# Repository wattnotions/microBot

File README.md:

# microBot
A tiny robot made using micro stepper motors

Here is a video of the v2 test PCB: 
https://www.youtube.com/watch?v=kQc0UNII-Kc

v3 will run on a 800mAh single cell lipo, esp32, lipo charger, tcrt5000 IR sensor, 2 H-bridge driver chips and a mini USB port
for programming and charging the battery.

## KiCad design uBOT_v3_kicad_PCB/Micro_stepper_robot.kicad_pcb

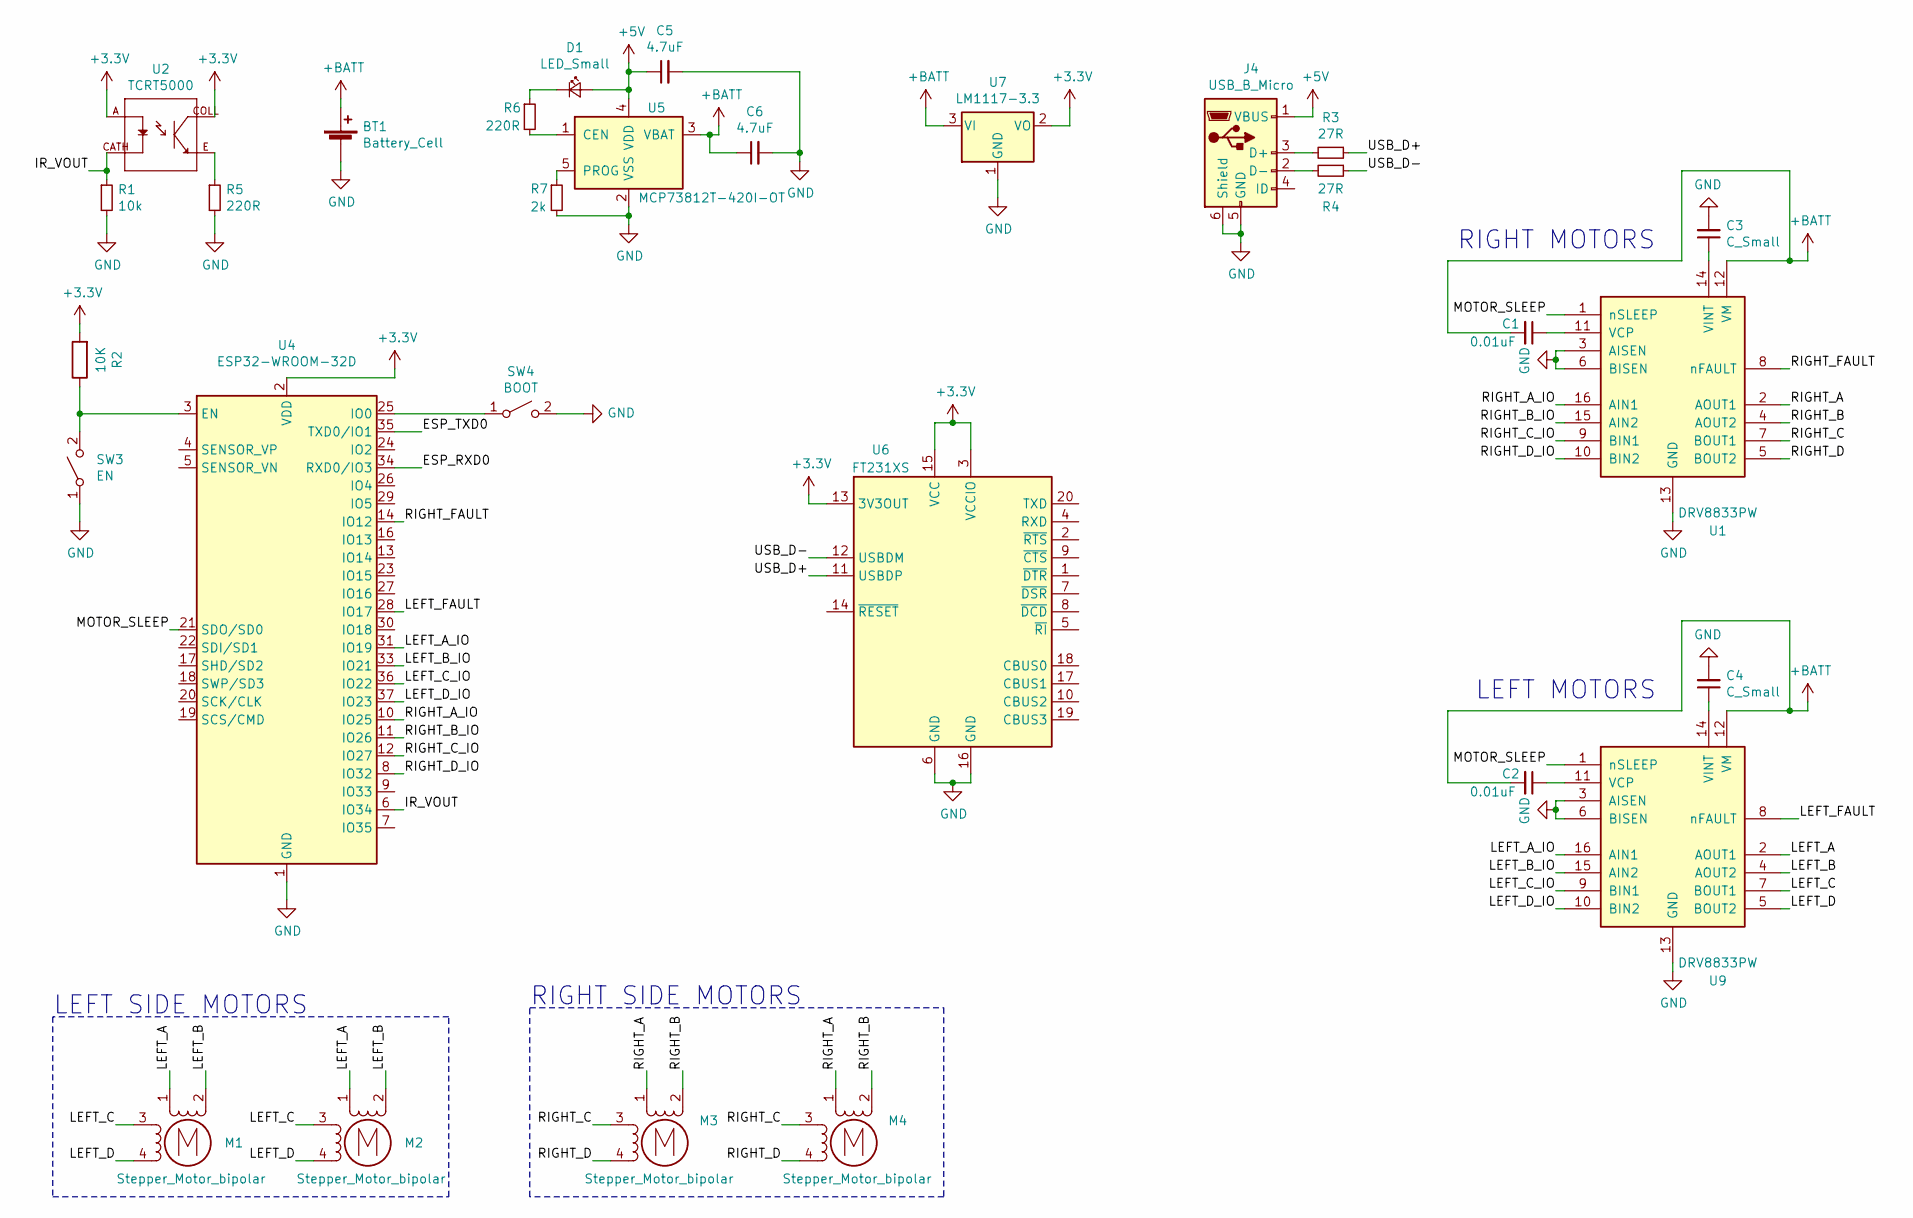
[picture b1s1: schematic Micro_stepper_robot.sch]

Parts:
BT1: Battery_Cell; Molex_PicoBlade_53398-0271_1x02-1MP_P1.25mm_Vertical
C1, C2: 0.01uF; C_0805_2012Metric_Pad1.15x1.40mm_HandSolder
C3, C4: C_Small; C_0805_2012Metric_Pad1.15x1.40mm_HandSolder
C5, C6: 4.7uF; C_0805_2012Metric_Pad1.15x1.40mm_HandSolder
D1: LED_Small; LED_0603_1608Metric
J4: USB_B_Micro; USB_Micro-B_Molex-105133-0001
M1, M2, M3, M4: Stepper_Motor_bipolar; micro_stepper1
R1: 10k; R_0805_2012Metric_Pad1.15x1.40mm_HandSolder
R2: 10K; R_0805_2012Metric_Pad1.15x1.40mm_HandSolder
R3, R4: 27R; R_0805_2012Metric_Pad1.15x1.40mm_HandSolder
R5, R6: 220R; R_0805_2012Metric_Pad1.15x1.40mm_HandSolder
R7: 2k; R_0805_2012Metric_Pad1.15x1.40mm_HandSolder
SW3: EN; SW_SPST_B3U-1000P
SW4: BOOT; SW_SPST_B3U-1000P
U1, U9: DRV8833PW; TSSOP-16_4.4x5mm_P0.65mm
U2: TCRT5000; OPTO_TCRT5000
U4: ESP32-WROOM-32D; ESP32-WROOM-32
U5: MCP73812T-420I-OT; SOT-23-5
U6: FT231XS; SSOP-20_3.9x8.7mm_P0.635mm
U7: LM1117-3.3; SOT-223-3_TabPin2

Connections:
+3V3: R2.2, U2.A, U2.COLL, U4.2 (VDD), U6.3 (VCCIO), U6.13 (3V3OUT), U6.15 (VCC), U7.2 (VO); also elsewhere on the board
+5V: C5.1, D1.2 (A), J4.1 (VBUS), U5.4 (VDD)
+BATT: BT1.1 (+), C1.2, C2.2, C6.1, U1.12 (VM), U5.3 (VBAT), U7.3 (VI), U9.12 (VM); also elsewhere on the board
/ESP_RXD0: U4.34 (RXD0/IO3)
/ESP_TXD0: U4.35 (TXD0/IO1)
/IR_VOUT: R1.1, U2.CATH, U4.6 (IO34)
/LEFT_A: M1.1, M2.1, U9.2 (AOUT1)
/LEFT_A_IO: U4.31 (IO19), U9.16 (AIN1)
/LEFT_B: M1.2 (-), M2.2 (-), U9.4 (AOUT2)
/LEFT_B_IO: U4.33 (IO21), U9.15 (AIN2)
/LEFT_C: M1.3, M2.3, U9.7 (BOUT1)
/LEFT_C_IO: U4.36 (IO22), U9.9 (BIN1)
/LEFT_D: M1.4, M2.4, U9.5 (BOUT2)
/LEFT_D_IO: U4.37 (IO23), U9.10 (BIN2)
/LEFT_FAULT: U4.28 (IO17), U9.8 (nFAULT)
/MOTOR_SLEEP: U1.1 (nSLEEP), U4.21 (SDO/SD0), U9.1 (nSLEEP)
/RIGHT_A: M3.1, M4.1, U1.2 (AOUT1)
/RIGHT_A_IO: U1.16 (AIN1), U4.10 (IO25)
/RIGHT_B: M3.2 (-), M4.2 (-), U1.4 (AOUT2)
/RIGHT_B_IO: U1.15 (AIN2), U4.11 (IO26)
/RIGHT_C: M3.3, M4.3, U1.7 (BOUT1)
/RIGHT_C_IO: U1.9 (BIN1), U4.12 (IO27)
/RIGHT_D: M3.4, M4.4, U1.5 (BOUT2)
/RIGHT_D_IO: U1.10 (BIN2), U4.8 (IO32)
/RIGHT_FAULT: U1.8 (nFAULT), U4.14 (IO12)
/USB_D+: R3.1, U6.11 (USBDP)
/USB_D-: R4.1, U6.12 (USBDM)
GND: BT1.2 (-), C3.2, C4.2, C5.2, C6.2, J4.5 (GND), J4.6 (Shield), R1.2, R5.2, R7.2, SW3.1 (A), SW4.2 (B), U1.3 (AISEN), U1.6 (BISEN), U1.13 (GND), U4.1 (GND), U4.15 (GND), U4.38 (GND), U4.39 (GND), U5.2 (VSS), U6.6 (GND), U6.16 (GND), U7.1 (GND), U9.3 (AISEN), U9.6 (BISEN), U9.13 (GND); also elsewhere on the board
unnamed: C1.1, U1.11 (VCP)
unnamed: C2.1, U9.11 (VCP)
unnamed: C3.1, U1.14 (VINT)
unnamed: C4.1, U9.14 (VINT)
unnamed: D1.1 (K), R6.1
unnamed: J4.2 (D-), R4.2
unnamed: J4.3 (D+), R3.2
unnamed: R2.1, SW3.2 (B), U4.3 (EN)
unnamed: R5.1, U2.E
unnamed: R6.2, U5.1 (CEN)
unnamed: R7.1, U5.5 (PROG)
unnamed: SW4.1 (A), U4.25 (IO0)

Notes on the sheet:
LEFT MOTORS
RIGHT MOTORS
LEFT SIDE MOTORS
RIGHT SIDE MOTORS

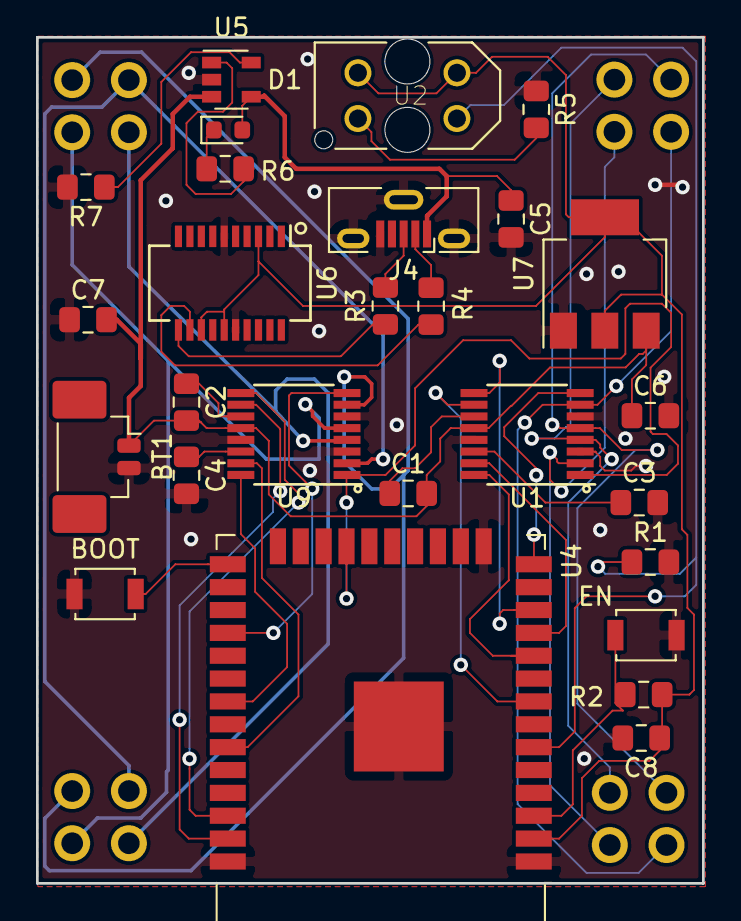
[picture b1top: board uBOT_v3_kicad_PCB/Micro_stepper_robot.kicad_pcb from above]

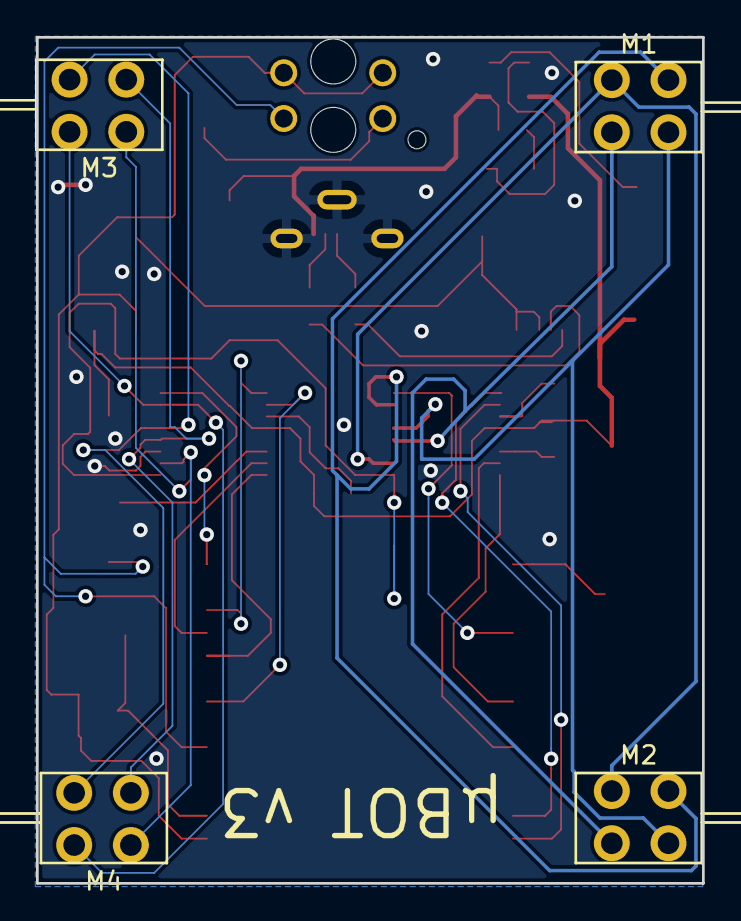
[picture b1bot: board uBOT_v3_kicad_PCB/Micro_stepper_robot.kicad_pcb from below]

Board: 2 copper layers, 37.0 x 47.0 mm, 31 parts (4 on the bottom side), 38 nets.

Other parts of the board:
C7, C8: 10uF; C_0805_2012Metric_Pad1.15x1.40mm_HandSolder

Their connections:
+3V3: C8.1; also elsewhere on the board
+BATT: C7.2; also elsewhere on the board
GND: C7.1, C8.2; also elsewhere on the board

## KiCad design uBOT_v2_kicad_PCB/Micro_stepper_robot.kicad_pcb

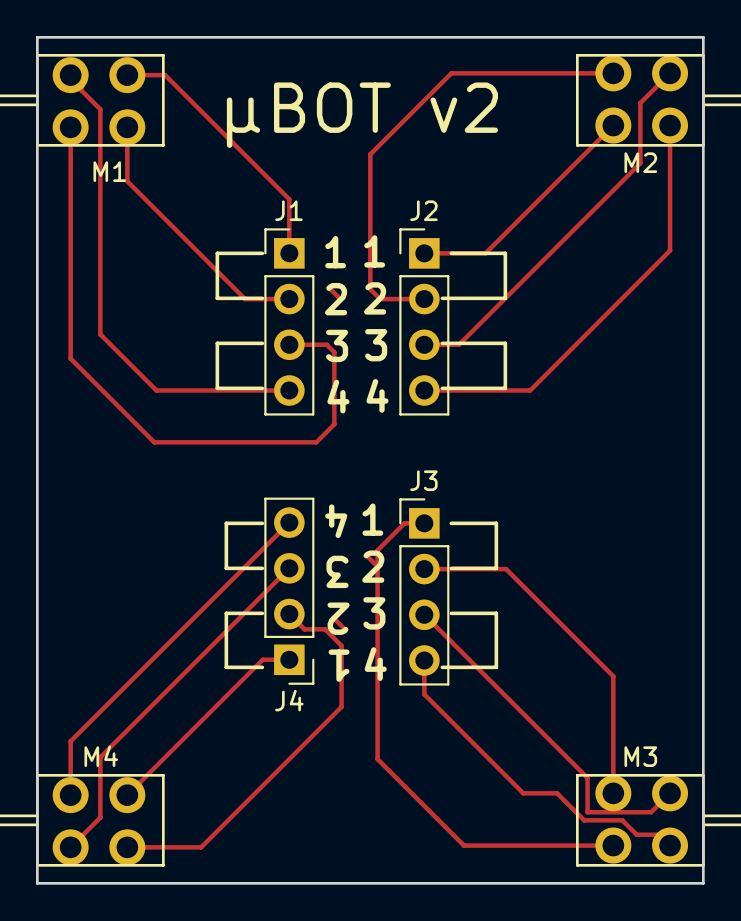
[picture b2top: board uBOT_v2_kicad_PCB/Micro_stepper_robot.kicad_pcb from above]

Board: 2 copper layers, 37.0 x 47.0 mm, 8 parts (0 on the bottom side), 16 nets.

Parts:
J1, J2, J3, J4: Conn_01x04_Male; PinHeader_1x04_P2.54mm_Vertical
M1, M2, M3, M4: Stepper_Motor_bipolar; micro_stepper1

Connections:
unnamed: J1.1, M1.2
unnamed: J1.2, M1.1
unnamed: J1.3, M1.3
unnamed: J1.4, M1.4
unnamed: J2.1, M2.2
unnamed: J2.2, M2.1
unnamed: J2.3, M2.3
unnamed: J2.4, M2.4
unnamed: J3.1, M3.2
unnamed: J3.2, M3.1
unnamed: J3.3, M3.3
unnamed: J3.4, M3.4
unnamed: J4.1, M4.2
unnamed: J4.2, M4.1
unnamed: J4.3, M4.3
unnamed: J4.4, M4.4

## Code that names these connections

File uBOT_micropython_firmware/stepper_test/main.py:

from machine import Pin
import time


print("IM IN MAIN")



la = 19
lb = 21
lc = 22
ld = 23

ra = 25
rb = 26
rc = 27
rd = 32


#Left side
#A and B are the same coil
left_a = Pin(la, Pin.OUT)    
left_b = Pin(lb, Pin.OUT)   

#C and D are the same coil
left_c = Pin(lc, Pin.OUT)    
left_d = Pin(ld, Pin.OUT)  

#Right side
#A and B are the same coil
right_a = Pin(ra, Pin.OUT)    
right_b = Pin(rb, Pin.OUT)   

#C and D are the same coil
right_c = Pin(rc, Pin.OUT)    
right_d = Pin(rd, Pin.OUT)   




def disable_steppers():
    left_a.value(0)
    left_b.value(0)
    left_c.value(0)
    left_d.value(0)
    
    right_a.value(0)
    right_b.value(0)
    right_c.value(0)
    right_d.value(0)
    print("Steppers disabled")
    
    
r_step_state = 1; 
def right_steppers(dir, msdelay): ##meant to be called in low latency loop
 
  if (r_step_state == 1):
    right_a.value(0)
    right_b.value(1)
    time.sleep_ms(msdelay)
    
  if (r_step_state == 2):
    right_c.value(0)
    right_d.value(1)
    time.sleep_ms(msdelay)
    
  if (r_step_state == 3):
    right_a.value(1)
    right_b.value(0)
    time.sleep_ms(msdelay)
  
  if (r_step_state == 4):
    right_c.value(1)
    right_d.value(0)
    time.sleep_ms(msdelay)
    
  if  (dir == 1) : r_step_state +=1 #going forward
  elif(dir == 0) : r_step_state -=1 #going backwards

l_step_state = 1 
def left_stepper(dir, msdelay):
  
  if (l_step_state == 1):
    left_a.value(0)
    left_b.value(1)
    time.sleep_ms(msdelay)
    
  if (l_step_state == 2):
    left_c.value(0)
    left_d.value(1)
    time.sleep_ms(msdelay)
    
  if (l_step_state == 3):
    left_a.value(1)
    left_b.value(0)
    time.sleep_ms(msdelay)
  
  if (l_step_state == 4):
    left_c.value(1)
    left_d.value(0)
    time.sleep_ms(msdelay)
    
  if  (dir == 1) : l_step_state +=1 #going forward
  elif(dir == 0) : l_step_state -=1 #going backwards

run_time = 0
start_time = time.time()
while (run_time < 10):
    run_time = time.time() - start_time
    left_stepper(1, 200)
    right_stepper(1,200)
from machine import Pin
import time


print("IM IN MAIN")

l_step_state = 1 
r_step_state = 1


la = 19
lb = 21
lc = 22
ld = 23

ra = 25
rb = 26
rc = 27
rd = 32


#Left side
#A and B are the same coil
left_a = Pin(la, Pin.OUT)    
left_b = Pin(lb, Pin.OUT)   

#C and D are the same coil
left_c = Pin(lc, Pin.OUT)    
left_d = Pin(ld, Pin.OUT)  

#Right side
#A and B are the same coil
right_a = Pin(ra, Pin.OUT)    
right_b = Pin(rb, Pin.OUT)   

#C and D are the same coil
right_c = Pin(rc, Pin.OUT)    
right_d = Pin(rd, Pin.OUT)   




def disable_steppers():
    left_a.value(0)
    left_b.value(0)
    left_c.value(0)
    left_d.value(0)
    
    right_a.value(0)
    right_b.value(0)
    right_c.value(0)
    right_d.value(0)
    print("Steppers disabled")
    
    
r_step_state = 1
def right_steppers(dir, msdelay): ##meant to be called in low latency loop
  global r_step_state
  if (r_step_state == 1):
    right_a.value(0)
    right_b.value(1)
    time.sleep_ms(msdelay)
    
  if (r_step_state == 2):
    right_c.value(0)
    right_d.value(1)
    time.sleep_ms(msdelay)
    
  if (r_step_state == 3):
    right_a.value(1)
    right_b.value(0)
    time.sleep_ms(msdelay)
  
  if (r_step_state == 4):
    right_c.value(1)
    right_d.value(0)
    time.sleep_ms(msdelay)
    
  if  (dir == 1) : r_step_state +=1 #going forward
  elif(dir == 0) : r_step_state -=1 #going backwards


def left_steppers(dir, msdelay):
  global l_step_state
  print(l_step_state)
  if (l_step_state == 1):
    
    left_a.value(0)
    left_b.value(1)
    time.sleep_ms(msdelay)
    
  if (l_step_state == 2):
    left_c.value(0)
    left_d.value(1)
    time.sleep_ms(msdelay)
    
  if (l_step_state == 3):
    left_a.value(1)
    left_b.value(0)
    time.sleep_ms(msdelay)
  
  if (l_step_state == 4):
    left_c.value(1)
    left_d.value(0)
    time.sleep_ms(msdelay)
    
  if  (dir == 1) : l_step_state +=1 #going forward
  elif(dir == 0) : l_step_state -=1 #going backwards

run_time = 0
start_time = time.time()
while (run_time < 10):
    run_time = time.time() - start_time
    left_steppers(1, 200)
   # right_steppers(1,200)
   
    
    
    
disable_steppers()
    
    
    
    
    




   
    
    
    
disable_steppers()
    
    
    
    
    

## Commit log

2020-03-16 cleaned up silk screen
2020-06-08 made holes bigger
2020-06-08 updated silkscreen to v2
2020-06-20 added some stepper test code
2020-06-21 changed dir structure, added v3 kicad project
2020-06-21 started v3 circuit design
2020-06-22 added h bridge drivers
2020-06-22 progressed schematic
2020-06-22 added ft231 datasheet
2020-06-22 started stepper motor schematic
2020-06-22 added datasheets
2020-06-22 added tcrt5000
2020-06-26 finished assigning footprints, started layout
2020-06-26 progressed layout
2020-06-29 completed rough footprint placement
2020-06-29 routing 75% completed
2020-06-29 routing completed :D
2020-06-29 put v3 silkscreen on botton
2020-06-29 silkscreen text final touch
2020-06-29 added filter caps to 3.3v and VBAT
2020-06-29 safety save
2020-06-29 fixed silk screen ref values
2020-07-13 left steppers working
2020-08-20 added wheel cad files
2021-02-07 left steppers in progress
2021-02-07 added debug print statements
2021-02-07 Left steppers working!
2021-02-07 added functions for left and right steppers rotation
2021-09-10 ADDED TX AND TX CONNECTIONS TO USB/UART IC
